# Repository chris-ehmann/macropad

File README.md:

# Macropad

I've been interested in mechanical keyboards for a while now, and recently I wanted to get a bit of experience writing firmware, so I decided to combine these two interests and create a mechanical keyboard from scratch (well, as close to "from scratch" as reasonably possible).

## Designing the PCB

The hardware design for a keyboard is fairly straightforward. A lot of credit here goes to ai03's guide located [here](https://wiki.ai03.com/books/pcb-design/), which gives pretty good direction on what a properly designed circuit should look like. Of course, I wanted to actually learn what was going on in the circuit that I was replicating, so I made sure to supplement this with reading through datasheets and general studying. I think I can confidently state what a pull-up resistor now does, at the very least.

Even though this is a 6-key keypad (which means each switch could be directly connected to it's own pin), I thought a keyboard matrix circuit would be more fun to implement. The premise here is pretty straightforward: since there aren't enough pins on microcontrollers to directly connect each switch to a key, you have to get a bit creative and arrange switches in a grid-like formation. Then, each switch will be connected to a specific grid pin and to a specific row pin. Now, say you have current flowing through a specific column, if any of the keys connected in that column are pressed, you'll be able to figure that out by simplying checking the corresponding row pins for any input. There's a few things to be considerate of however -- primarily [ghosting](https://www.dribin.org/dave/keyboard/one_html/).

## Soldering

I've never soldered before, so I thought this would be a great opportunity to learn. There's a few components that I thought would be near impossible for me to solder as a beginner (e.g., the USB Micro-B connector, the ATMEGA32U4 microcontroller, and whatever other SMD  components), so I opted for these to be assembled by the PCB manufacturer (in my case, JLCPCB). The switches however, being through-hole, felt a little bit more in my ballpark. 

For soldering equipment, I didn't have anything on hand so I ended up grabbing myself a [PINECIL](https://pine64.com/product/pinecil-smart-mini-portable-soldering-iron/). It seems to be pretty highly recommended and I can understand why; it felt very easy to use. Maybe in the future if I do more soldering I might pick up something more heavy-duty, like a hot air rework station.

## Firmware

The firmware I've written for this uses [LUFA](https://github.com/abcminiuser/lufa) to communicate via USB. I'm new to this framework, so I've built upon the Keyboard demo that's generously provided with LUFA. The relevant keypad code (e.g. what actually sets up our pins, scans through the matrix, handles debouncing, etc.) can be found in `macropad_firmware/macropad_firmware/Keyboard.c`. I do eventually want to move this out of a demo and into something built up from scratch (albeit while still using LUFA), but for now this has worked very well for a first revision.

The firmware is pretty basic: for scanning the matrix, we set each row to output LOW, and then we scan each column (configured to be input with pull-up resistor active) to detect which keys are pressed. We then store the number of scan-cycles a key has been pressed for, and once it hits some debouncing threshold (I've chosen 10, which corresponds to about a 5ms debounce period. The datasheet for the Cherry-MX Brown switches that I'm using state that the bounce time is <2 msec, so it's slightly overkill) we can then send it over in the next USB report.

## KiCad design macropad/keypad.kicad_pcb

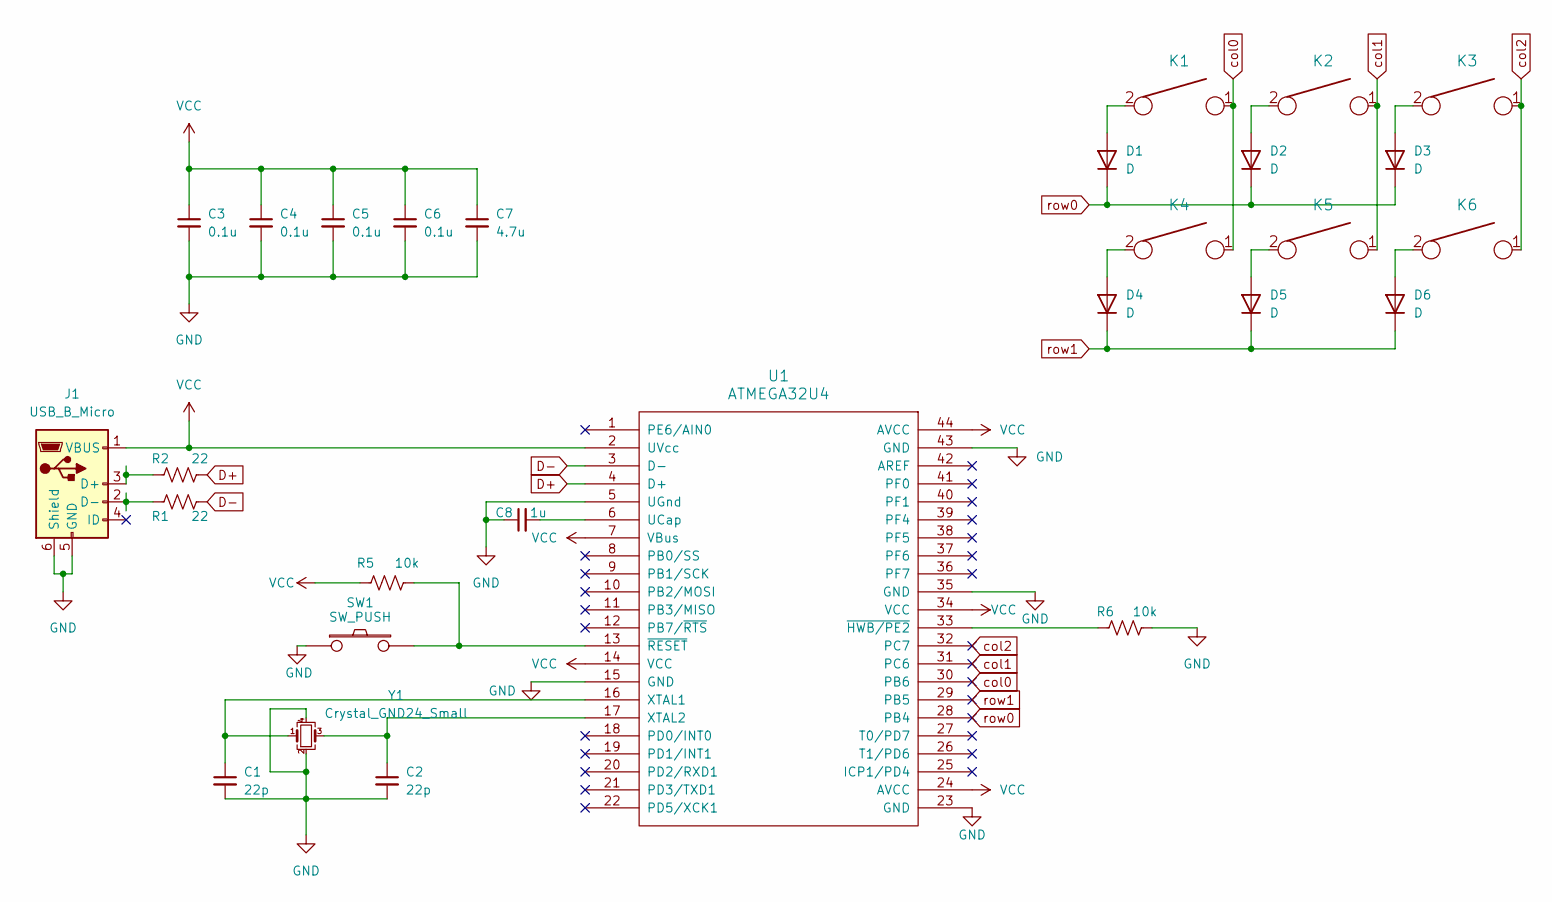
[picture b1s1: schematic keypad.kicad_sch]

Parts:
C1, C2: 22p; C_0805_2012Metric_Pad1.18x1.45mm_HandSolder
C3, C4, C5, C6: 0.1u; C_0805_2012Metric_Pad1.18x1.45mm_HandSolder
C7: 4.7u; C_0805_2012Metric_Pad1.18x1.45mm_HandSolder
C8: 1u; C_0805_2012Metric_Pad1.18x1.45mm_HandSolder
D1, D2, D3, D4, D5, D6: D; D_SOD-123
J1: USB_B_Micro; USB_Micro-B_Molex-105017-0001
K1, K2, K3, K4, K5, K6: KEYSW; SW_Cherry_MX_1.00u_PCB
R1, R2: 22; R_0805_2012Metric_Pad1.20x1.40mm_HandSolder
R5, R6: 10k; R_0805_2012Metric_Pad1.20x1.40mm_HandSolder
SW1: SW_PUSH; SW_SPST_TL3342
U1: ATMEGA32U4; TQFP-44_10x10mm_P0.8mm
Y1: Crystal_GND24_Small; Crystal_SMD_3225-4Pin_3.2x2.5mm_HandSoldering

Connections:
D+: R2.2, U1.4 (D+)
D-: R1.2, U1.3 (D-)
GND: C1.2, C2.2, C3.2, C4.2, C5.2, C6.2, C7.2, C8.1, J1.5 (GND), J1.6 (Shield), R6.2, SW1.1, U1.5 (UGnd), U1.15 (GND), U1.23 (GND), U1.35 (GND), U1.43 (GND), Y1.2, Y1.4
unnamed: D1.2 (A), K1.2
unnamed: D2.2 (A), K2.2
unnamed: D3.2 (A), K3.2
unnamed: D4.2 (A), K4.2
unnamed: D5.2 (A), K5.2
unnamed: D6.2 (A), K6.2
unnamed: J1.3 (D+), R2.1
unnamed: J1.2 (D-), R1.1
unnamed: C8.2, U1.6 (UCap)
unnamed: C1.1, U1.16 (XTAL1), Y1.1
unnamed: C2.1, U1.17 (XTAL2), Y1.3
unnamed: R6.1, U1.33 (~HWB/PE2)
unnamed: R5.2, SW1.2, U1.13 (~RESET)
VCC: C3.1, C4.1, C5.1, C6.1, C7.1, J1.1 (VBUS), R5.1, U1.2 (UVcc), U1.7 (VBus), U1.14 (VCC), U1.24 (AVCC), U1.34 (VCC), U1.44 (AVCC)
col0: K1.1, K4.1, U1.30 (PB6)
col1: K2.1, K5.1, U1.31 (PC6)
col2: K3.1, K6.1, U1.32 (PC7)
row0: D1.1 (K), D2.1 (K), D3.1 (K), U1.28 (PB4)
row1: D4.1 (K), D5.1 (K), D6.1 (K), U1.29 (PB5)

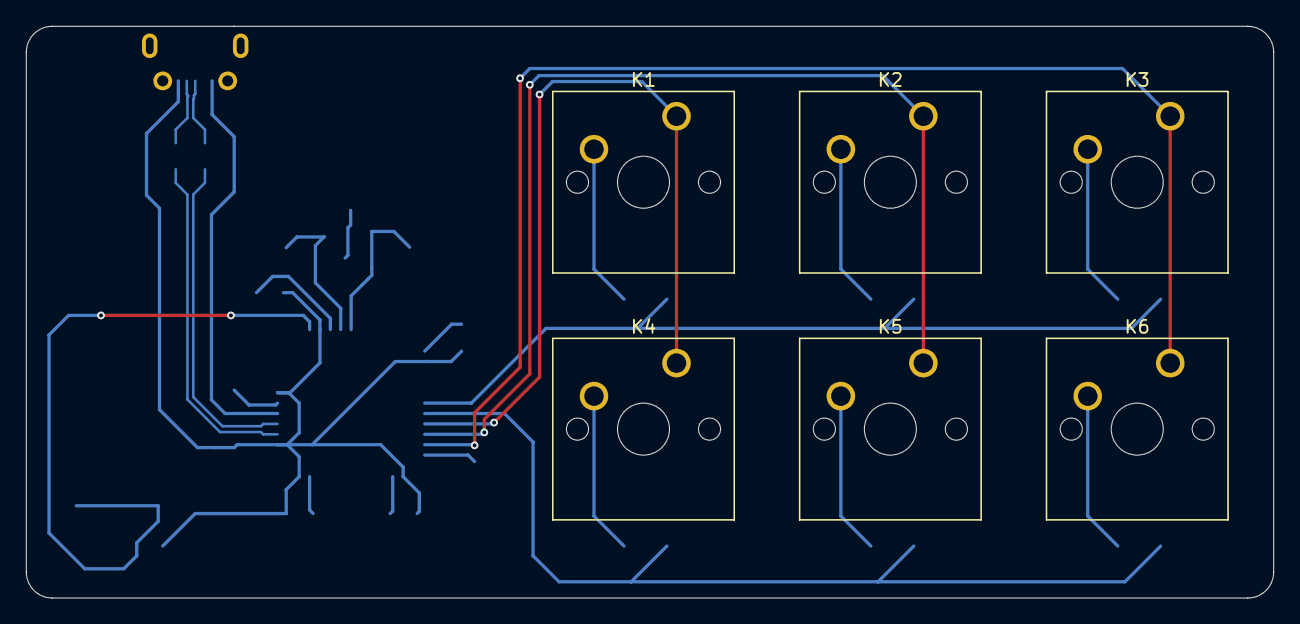
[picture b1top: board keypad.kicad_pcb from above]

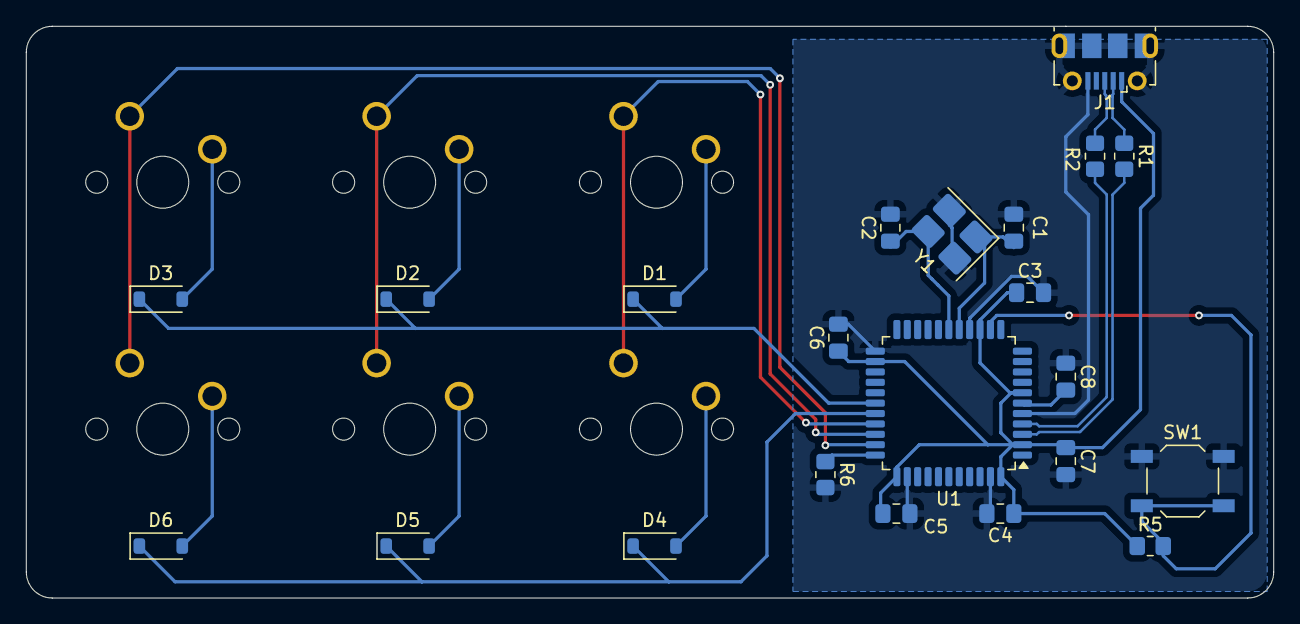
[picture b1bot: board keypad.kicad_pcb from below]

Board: 2 copper layers, 96.0 x 44.0 mm, 28 parts (22 on the bottom side), 22 nets.

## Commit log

2025-12-17 Add KiCad files
    Includes schematic and PCB
2025-12-17 Add PCB and schematic image
2025-12-20 Add firmware
